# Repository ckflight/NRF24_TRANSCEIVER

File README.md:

# NRF24_TRANSCEIVER

This is a small board including KL27Z MCU, NRF24 2.4Ghz Transceiver IC and RFX2401C Front End with Power Amplifier for transmission and Low Noise Amplifier for reception.

A simple firmware for NRF24 usage with baremetal library implementation is included in firmware folder.

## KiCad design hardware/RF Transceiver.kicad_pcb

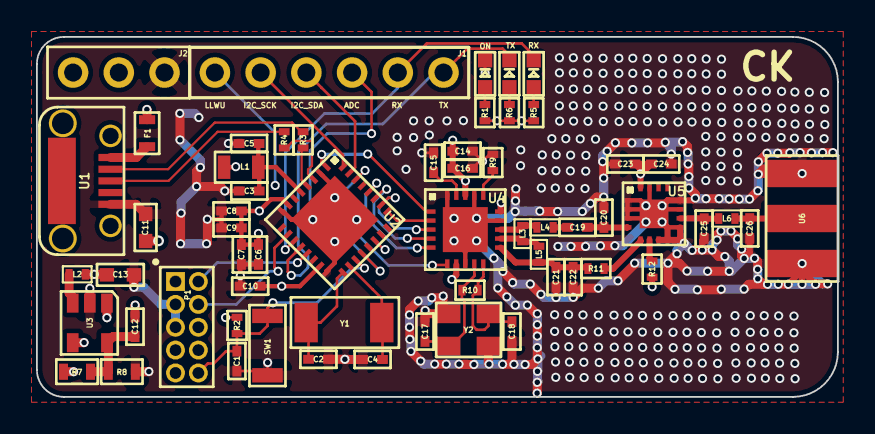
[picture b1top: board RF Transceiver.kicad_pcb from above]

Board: 4 copper layers, 44.5 x 20.0 mm, 60 parts (0 on the bottom side), 44 nets.

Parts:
C1, C5, C7, C9, C10, C24: 0.1uF; C_0402
C2, C4, C17, C18: 15pF; C_0402
C3: 2.2uF; C_0402
C6, C8: 1uF; C_0402
C11, C13: 22uF; C_0603
C12: 22pF; C_0402
C14, C23: 10nF; C_0402
C15: 33nF; C_0402
C16: 1nF; C_0402
C19: 1.5pF; C_0402
C20: 1pF; C_0402
C21: 2.2nF; C_0402
C22: 4.7pF; C_0402
C25, C26: 2pF; C_0402
F1: Fuse_Small; R_0603
J1: GPIO; Pin_Header_Straight_1x06_Pitch2.54mm
J2: POWER; Pin_Header_Straight_1x03_Pitch2.54mm
L1: 330 Ohm; L_0805
L2: 2.2uH; L_0402
L3: 8.2nH; L_0402
L4: 3.9nH; L_0402
L5: 2.7nH; L_0402
L6: 1.5nH; L_0402
ON: LED_Small; LED_0603
P1: SWD/JTAG; Pin_Header_Straight_2x05_Pitch1.27mm
R1, R11, R12: 1K; R_0402
R2: 10K; R_0402
R3, R4, R5, R6: 33; R_0402
R7: 470K; R_0603
R8: 105K; R_0603
R9: 22K; R_0402
R10: 1M; R_0402
RX: LED_Small; LED_0603
SW1: RST_Button; B3U_Button
TX: LED_Small; LED_0603
U1: MICRO-USB-B; USB_MicroB-TH
U2: MKL27Z64VFM4; QFN32-1EXP_5x5mm_Pitch0.5mm
U3: AP3429AKTTR; SOT-23-5
U4: nRF24L01P-R7; QFN20-1EXP_4x4mm_Pitch0.5mm
U5: RFX2401C; QFN16-1EXP_3x3mm_Pitch0.5mm
U6: SMA_CONN
Y1: 32.768Khz
Y2: 16Mhz

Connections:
3.3V: C6.1, C7.1, C8.1, C9.1, C10.1, C12.1, C13.1, C14.1, C16.1, C23.1, C24.2, J2.2, L1.1, L2.2, P1.1, R1.2, R2.1, R5.2, R6.2, R7.1, R12.2, U2.7, U2.15, U4.7, U4.15, U4.18, U5.16
5V: C11.1, F1.2, J2.3, U3.1, U3.4
ADC: J1.3, U2.20
CE: U2.1, U4.1
CSN: U2.25, U4.2
GND: C1.2, C2.2, C3.2, C4.2, C5.2, C6.2, C7.2, C8.2, C9.2, C10.2, C11.2, C13.2, C14.2, C15.2, C16.2, C17.1, C18.1, C20.1, C21.2, C22.2, C23.2, C24.1, C25.2, C26.2, J2.1, ON.1, P1.3, P1.5, R8.2, R9.2, SW1.1, U1.5, U2.2, U2.8, U2.16, U2.33, U3.2, U4.8, U4.14, U4.17, U4.20, U4.21, U5.1, U5.2, U5.3, U5.7, U5.8, U5.9, U5.11, U5.12, U5.15, U5.17, U6.2, U6.3, U6.4, U6.5, Y2.2, Y2.4
I2C1_SCK: J1.5, U2.32
I2C1_SDA: J1.4, U2.31
IRQn: U2.30, U4.6
unnamed: C2.1, U2.17, Y1.2
unnamed: C4.1, U2.18, Y1.1
unnamed: C12.2, R7.2, R8.1, U3.5
unnamed: C15.1, U4.19
unnamed: C17.2, R10.1, U4.9, Y2.1
unnamed: C18.2, R10.2, U4.10, Y2.3
unnamed: C19.1, C20.2, U5.4
unnamed: C19.2, L4.2
unnamed: C21.1, C22.1, L5.2, R11.2, U4.11
unnamed: C25.1, L6.2, U5.10
unnamed: C26.1, L6.1, U6.1
unnamed: F1.1, U1.1
unnamed: L2.1, U3.3
unnamed: L3.1, L5.1, U4.12
unnamed: L3.2, L4.1, U4.13
unnamed: ON.2, R1.1
unnamed: R3.1, U1.2
unnamed: R4.1, U1.3
unnamed: R5.1, RX.2
unnamed: R6.1, TX.2
unnamed: R9.1, U4.16
unnamed: R11.1, U5.5
unnamed: R12.1, U5.6
RESET: C1.1, P1.10, R2.2, SW1.2, U2.19
RX: J1.2, RX.1, U2.11
SPI_MISO: U2.28, U4.5
SPI_MOSI: U2.27, U4.4
SPI_SCK: U2.26, U4.3
SWD_CLK: P1.4, U2.10
SWD_DIO: P1.2, U2.13
TPM0_CH0/LLWU_P6: J1.6, U2.22
TX: J1.1, TX.1, U2.12
USB_M: R3.2, U2.4
USB_P: R4.2, U2.3
USB_VDD: C3.1, C5.1, L1.2, U2.5
